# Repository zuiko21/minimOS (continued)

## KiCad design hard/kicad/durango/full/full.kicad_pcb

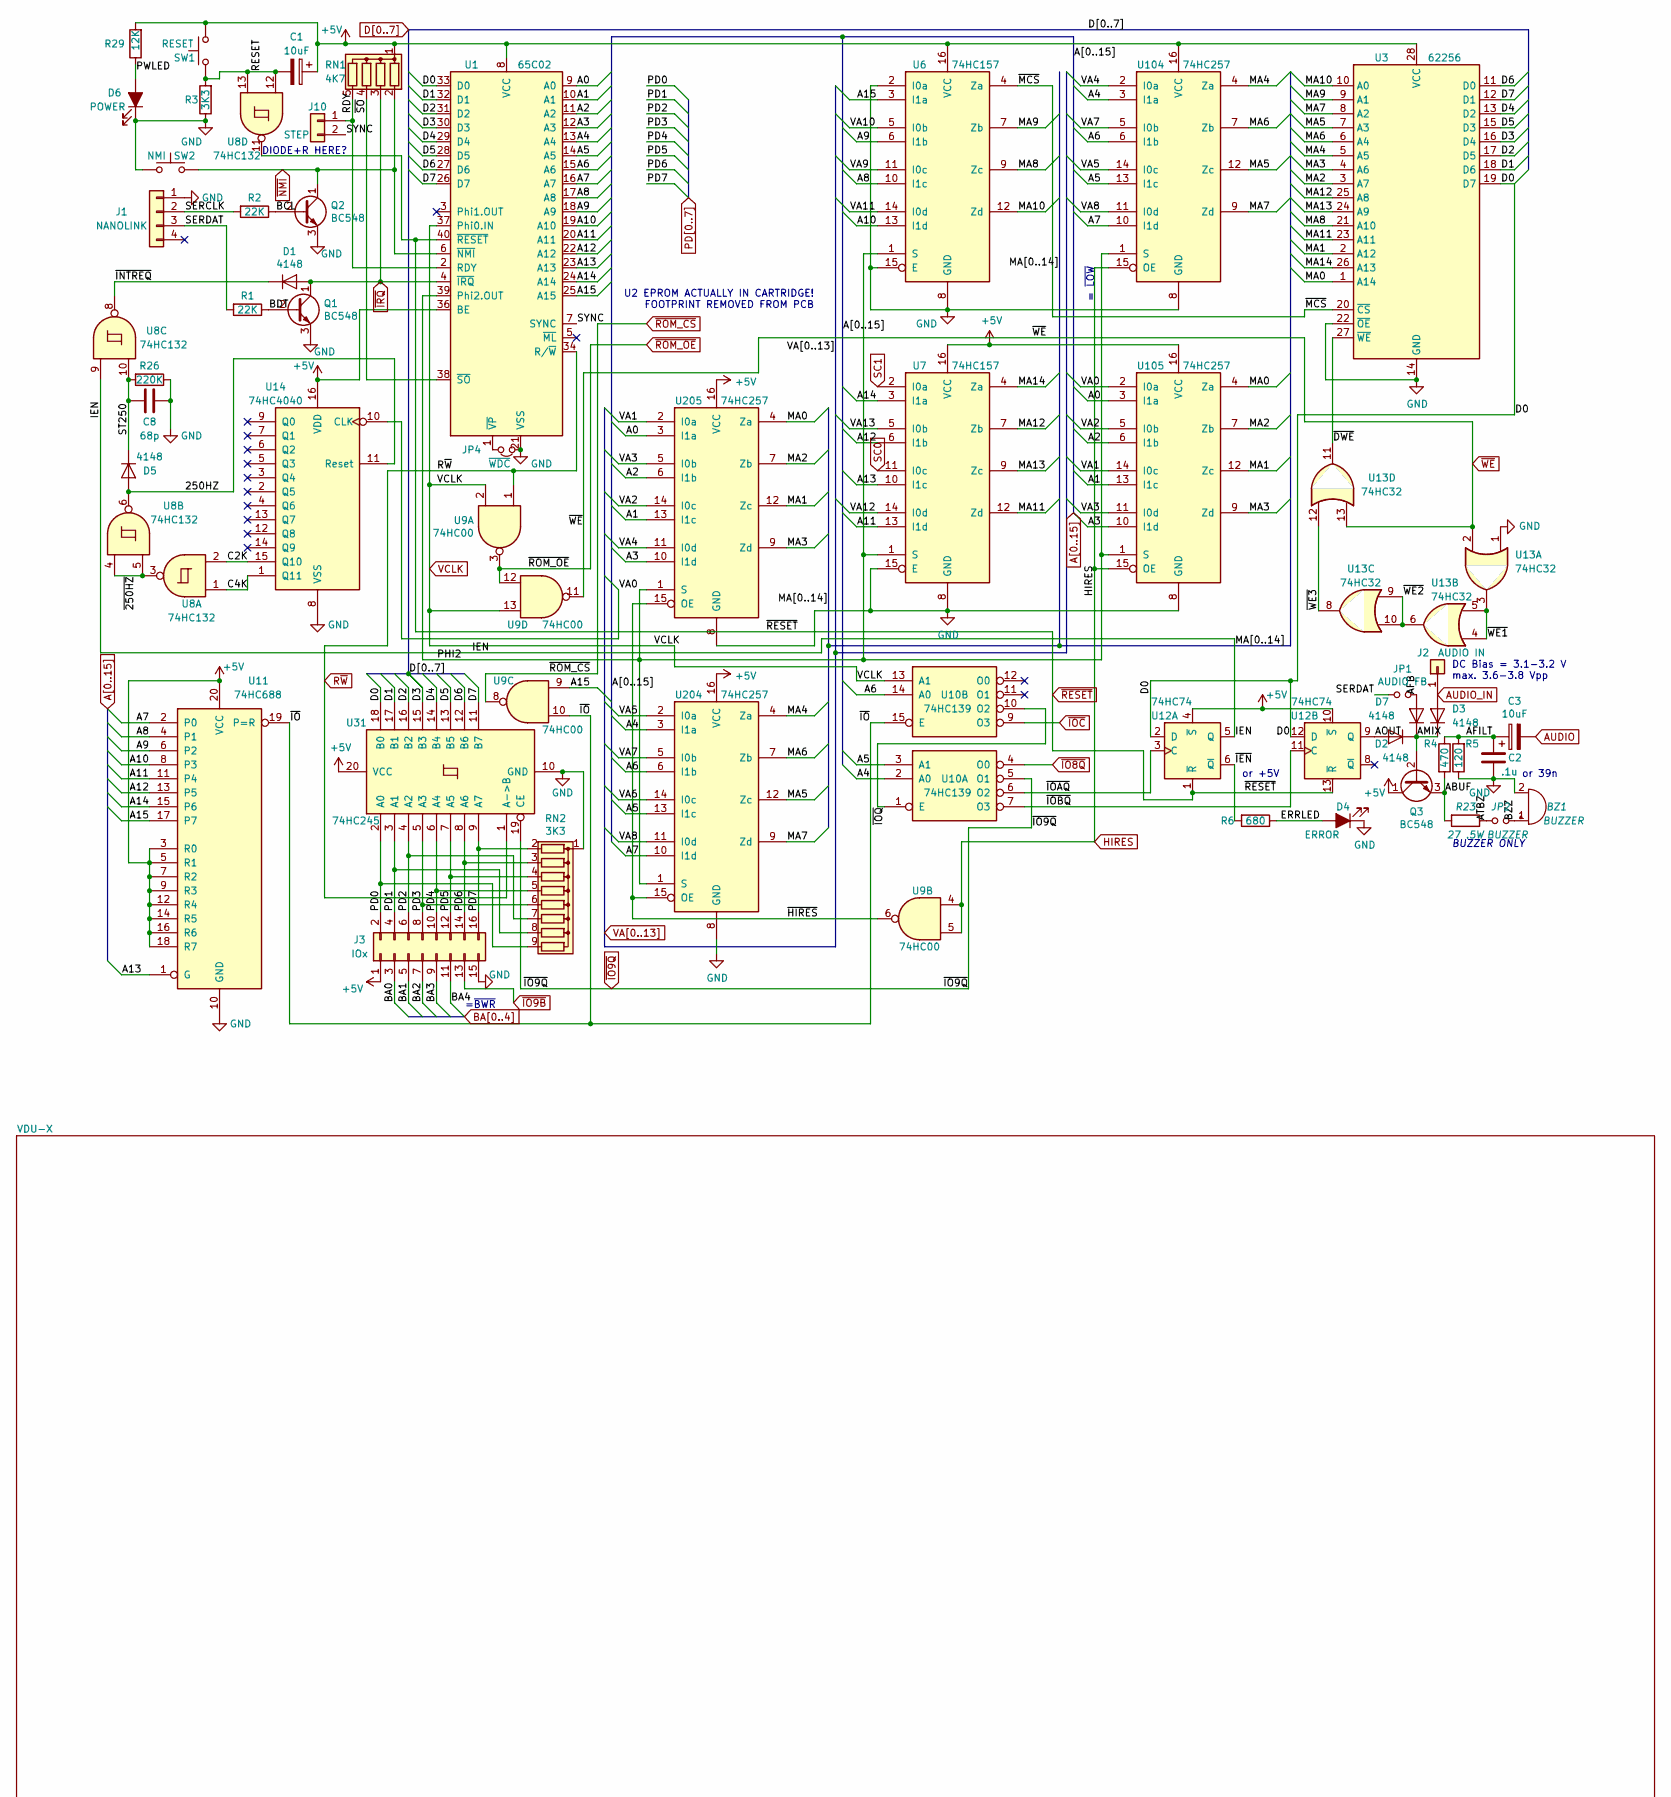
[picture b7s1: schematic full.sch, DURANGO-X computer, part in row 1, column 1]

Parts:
BZ1: BUZZER; Buzzer_12x9.5RM7.6
C1, C3: 10uF; CP_Radial_D4.0mm_P1.50mm
C2: .1u; C_Rect_L7.2mm_W2.5mm_P5.00mm_FKS2_FKP2_MKS2_MKP2
C8: 68p; C_Disc_D3.8mm_W2.6mm_P2.50mm
D1, D2, D3, D5, D7: 4148; D_DO-35_SOD27_P2.54mm_Vertical_KathodeUp
D4: ERROR; LED_D3.0mm_Clear
D6: POWER; LED_D3.0mm_Clear
J1: NANOLINK; PinHeader_1x04_P2.54mm_Vertical
J2: AUDIO IN; PinHeader_1x01_P2.54mm_Vertical
J3: IOx; IDC-Header_2x08_P2.54mm_Vertical
J10: STEP; PinHeader_1x02_P2.54mm_Vertical
JP1: AUDIO FB; PinHeader_1x02_P2.54mm_Vertical
JP2: BUZZER; PinHeader_1x02_P2.54mm_Vertical
JP4: ~WDC; SolderJumper-2_P1.3mm_Open_RoundedPad1.0x1.5mm
Q1, Q2, Q3: BC548; TO-92_Inline
R1, R2: 22K; R_Axial_DIN0207_L6.3mm_D2.5mm_P2.54mm_Vertical
R3: 3K3; R_Axial_DIN0207_L6.3mm_D2.5mm_P2.54mm_Vertical
R4: 470; R_Axial_DIN0207_L6.3mm_D2.5mm_P2.54mm_Vertical
R5: 120; R_Axial_DIN0207_L6.3mm_D2.5mm_P2.54mm_Vertical
R6: 680; R_Axial_DIN0207_L6.3mm_D2.5mm_P2.54mm_Vertical
R23: 27 .5W; R_Axial_DIN0309_L9.0mm_D3.2mm_P2.54mm_Vertical
R26: 220K; R_Axial_DIN0207_L6.3mm_D2.5mm_P2.54mm_Vertical
R29: 12K; R_Axial_DIN0207_L6.3mm_D2.5mm_P2.54mm_Vertical
RN1: 4K7; R_Array_SIP5
RN2: 3K3; R_Array_SIP9
SW1: RESET; SW_PUSH_6mm
SW2: NMI; SW_PUSH_6mm
U1: 65C02; DIP-40_W15.24mm_Socket
U3: 62256; DIP-28_W15.24mm_Socket
U6, U7: 74HC157; DIP-16_W7.62mm_Socket
U8: 74HC132; DIP-14_W7.62mm_Socket
U9: 74HC00; DIP-14_W7.62mm_Socket
U10: 74HC139; DIP-16_W7.62mm_Socket
U11: 74HC688; DIP-20_W7.62mm_Socket
U12: 74HC74; DIP-14_W7.62mm_Socket
U13: 74HC32; DIP-14_W7.62mm_Socket
U14: 74HC4040; DIP-16_W7.62mm_Socket
U31: 74HC245; DIP-20_W7.62mm_Socket
U104, U105, U204, U205: 74HC257; DIP-16_W7.62mm_Socket

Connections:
+5V: C1.1, J3.1, Q3.1 (C), R29.2, RN1.1 (common), SW1.2, U1.8 (VCC), U1.36 (BE), U3.28 (VCC), U6.16 (VCC), U7.16 (VCC), U11.3 (R0), U11.5 (R1), U11.7 (R2), U11.9 (R3), U11.12 (R4), U11.14 (R5), U11.16 (R6), U11.18 (R7), U11.20 (VCC), U12.4 (~S), U12.10 (~S), U14.16 (VDD), U31.20 (VCC), U104.16 (VCC), U105.16 (VCC), U204.16 (VCC), U205.16 (VCC); also elsewhere on the board
/250HZ: D5.2 (A), U8.6, U14.11 (Reset)
/ABUF: Q3.3 (E), R4.2, R23.2
/AFB: D7.2 (A), JP1.2
/AFILT: C2.1, C3.1, R4.1, R5.2
/AMIX: D2.1 (K), D3.1 (K), D7.1 (K), Q3.2 (B)
/AOUT: D2.2 (A), U12.9 (Q)
/ATBZ: JP2.1, R23.1
/BCL: Q2.2 (B), R2.1
/BDT: Q1.2 (B), R1.1
/BZZ: BZ1.1 (-), JP2.2
/C2K: U8.2, U14.15 (Q10)
/C4K: U8.1, U14.1 (Q11)
/ERRLED: D4.2 (A), R6.1
/IEN: U8.9, U12.5 (Q)
/MA0: U3.1 (A14), U105.4 (Za), U205.4 (Za)
/MA1: U3.2 (A12), U105.12 (Zc), U205.12 (Zc)
/MA2: U3.3 (A7), U105.7 (Zb), U205.7 (Zb)
/MA3: U3.4 (A6), U105.9 (Zd), U205.9 (Zd)
/MA4: U3.5 (A5), U104.4 (Za), U204.4 (Za)
/MA5: U3.7 (A3), U104.12 (Zc), U204.12 (Zc)
/MA6: U3.6 (A4), U104.7 (Zb), U204.7 (Zb)
/MA7: U3.8 (A2), U104.9 (Zd), U204.9 (Zd)
/MA8: U3.21 (A10), U6.9 (Zc)
/MA9: U3.9 (A1), U6.7 (Zb)
/MA10: U3.10 (A0), U6.12 (Zd)
/MA11: U3.23 (A11), U7.12 (Zd)
/MA12: U3.25 (A8), U7.7 (Zb)
/MA13: U3.24 (A9), U7.9 (Zc)
/MA14: U3.26 (A13), U7.4 (Za)
/PHI2: U1.39 (Phi2.OUT), U6.1 (S), U7.1 (S), U104.1 (S), U105.1 (S), U204.1 (S), U205.1 (S)
/PWLED: D6.2 (A), R29.1
/RDY: J10.1, RN1.5 (R4), U1.2 (RDY)
/RESET: C1.2, R3.2, SW1.1, U8.12, U8.13
/SERCLK: J1.2, R2.2
/SERDAT: J1.3, JP1.1, R1.2
/ST250: C8.2, D5.1 (K), R26.2, U8.10
/SYNC: J10.2, U1.7 (SYNC)
/~250HZ: U8.3, U8.4, U8.5
/~DWE: U3.27 (~WE~), U13.11
/~HIRES: U9.6, U204.15 (OE), U205.15 (OE)
/~IEN: R6.2, U12.6 (~Q)
/~INTREQ: D1.1 (K), U8.8
/~IO: U9.10, U10.15 (E), U11.19 (P=R)
/~IOAQ: U10.6 (O2), U12.3 (C)
/~IOBQ: U10.7 (O3), U12.11 (C)
/~IOQ: U10.1 (E), U10.10 (O2)
/~MCS: U3.20 (~CS), U6.4 (Za)
/~SO: RN1.4 (R3), U1.38 (~SO)
/~WE1: U13.3, U13.4, U13.5
/~WE2: U13.6, U13.9, U13.10
/~WE3: U13.8, U13.12
A0: U1.9 (A0), U105.3 (I1a), U205.3 (I1a); also elsewhere on the board
A1: U1.10 (A1), U105.13 (I1c), U205.13 (I1c); also elsewhere on the board
A2: U1.11 (A2), U105.6 (I1b), U205.6 (I1b); also elsewhere on the board
A3: U1.12 (A3), U105.10 (I1d), U205.10 (I1d); also elsewhere on the board
A4: U1.13 (A4), U10.2 (A0), U104.3 (I1a), U204.3 (I1a); also elsewhere on the board
A5: U1.14 (A5), U10.3 (A1), U104.13 (I1c), U204.13 (I1c); also elsewhere on the board
A6: U1.15 (A6), U10.14 (A0), U104.6 (I1b), U204.6 (I1b); also elsewhere on the board
A7: U1.16 (A7), U11.2 (P0), U104.10 (I1d), U204.10 (I1d); also elsewhere on the board
A8: U1.17 (A8), U6.10 (I1c), U11.4 (P1); also elsewhere on the board
A9: U1.18 (A9), U6.6 (I1b), U11.6 (P2); also elsewhere on the board
A10: U1.19 (A10), U6.13 (I1d), U11.8 (P3); also elsewhere on the board
A11: U1.20 (A11), U7.13 (I1d), U11.11 (P4); also elsewhere on the board
A12: U1.22 (A12), U7.6 (I1b), U11.13 (P5); also elsewhere on the board
A13: U1.23 (A13), U7.10 (I1c), U11.1 (G); also elsewhere on the board
A14: U1.24 (A14), U7.3 (I1a), U11.15 (P6); also elsewhere on the board
A15: U1.25 (A15), U6.3 (I1a), U9.9, U11.17 (P7); also elsewhere on the board
AUDIO: C3.2; also elsewhere on the board
AUDIO_IN: D3.2 (A), J2.1; also elsewhere on the board
BA0: J3.3; also elsewhere on the board
BA1: J3.5; also elsewhere on the board
BA2: J3.7; also elsewhere on the board
BA3: J3.9; also elsewhere on the board
BA4: J3.11; also elsewhere on the board
D0: U1.33 (D0), U3.19 (D7), U12.2 (D), U12.12 (D), U31.18 (B0); also elsewhere on the board
D1: U1.32 (D1), U3.18 (D6), U31.17 (B1); also elsewhere on the board
D2: U1.31 (D2), U3.17 (D5), U31.16 (B2); also elsewhere on the board
D3: U1.30 (D3), U3.16 (D4), U31.15 (B3); also elsewhere on the board
D4: U1.29 (D4), U3.13 (D2), U31.14 (B4); also elsewhere on the board
D5: U1.28 (D5), U3.15 (D3), U31.13 (B5); also elsewhere on the board
D6: U1.27 (D6), U3.11 (D0), U31.12 (B6); also elsewhere on the board
D7: U1.26 (D7), U3.12 (D1), U31.11 (B7); also elsewhere on the board
HIRES: U9.4, U9.5, U104.15 (OE), U105.15 (OE); also elsewhere on the board
unnamed: JP4.1, U1.1 (~VP)
PD0: J3.2, RN2.9 (R8), U31.2 (A0); also elsewhere on the board
PD1: J3.4, RN2.8 (R7), U31.3 (A1); also elsewhere on the board
PD2: J3.6, RN2.7 (R6), U31.4 (A2); also elsewhere on the board
PD3: J3.8, RN2.6 (R5), U31.5 (A3); also elsewhere on the board
PD4: J3.10, RN2.5 (R4), U31.6 (A4); also elsewhere on the board
PD5: J3.12, RN2.4 (R3), U31.7 (A5); also elsewhere on the board
PD6: J3.14, RN2.3 (R2), U31.8 (A6); also elsewhere on the board
PD7: J3.16, RN2.2 (R1), U31.9 (A7); also elsewhere on the board
R~W: U1.34 (R/~W), U9.1, U31.1 (A->B); also elsewhere on the board
SC0: U7.11 (I0c); also elsewhere on the board
SC1: U7.2 (I0a); also elsewhere on the board
VA0: U14.10 (CLK), U105.2 (I0a); also elsewhere on the board
VA1: U105.14 (I0c), U205.2 (I0a); also elsewhere on the board
VA2: U105.5 (I0b), U205.14 (I0c); also elsewhere on the board
VA3: U105.11 (I0d), U205.5 (I0b); also elsewhere on the board
VA4: U104.2 (I0a), U205.11 (I0d); also elsewhere on the board
VA5: U104.14 (I0c), U204.2 (I0a); also elsewhere on the board
VA6: U204.14 (I0c); also elsewhere on the board
VA7: U104.5 (I0b), U204.5 (I0b); also elsewhere on the board
VA8: U104.11 (I0d), U204.11 (I0d); also elsewhere on the board
VA9: U6.11 (I0c); also elsewhere on the board
VA10: U6.5 (I0b); also elsewhere on the board
VA11: U6.14 (I0d); also elsewhere on the board
VA12: U7.14 (I0d); also elsewhere on the board
VA13: U7.5 (I0b); also elsewhere on the board
VCLK: U1.37 (Phi0.IN), U9.2, U9.13, U10.13 (A1); also elsewhere on the board
~IO8Q: U10.4 (O0); also elsewhere on the board
~IO9B: J3.13; also elsewhere on the board
~IOC: U10.9 (O3); also elsewhere on the board
~IRQ: D1.2 (A), Q1.1 (C), RN1.3 (R2), U1.4 (~IRQ); also elsewhere on the board
~NMI: Q2.1 (C), RN1.2 (R1), SW2.1, U1.6 (~NMI); also elsewhere on the board
~RESET: U1.40 (~RESET), U8.11, U12.1 (~R), U12.13 (~R); also elsewhere on the board
~ROM_CS: U9.8; also elsewhere on the board
~ROM_OE: U9.3, U9.12; also elsewhere on the board
~WE: U9.11, U13.2, U13.13; also elsewhere on the board

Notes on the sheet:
BUZZER ONLY
DC Bias = 3.1-3.2 V max. 3.6-3.8 Vpp
or 39n
DIODE+R HERE?
or +5V
U2 EPROM ACTUALLY IN CARTRIDGE! FOOTPRINT REMOVED FROM PCB
=~BWR
= ~LOW

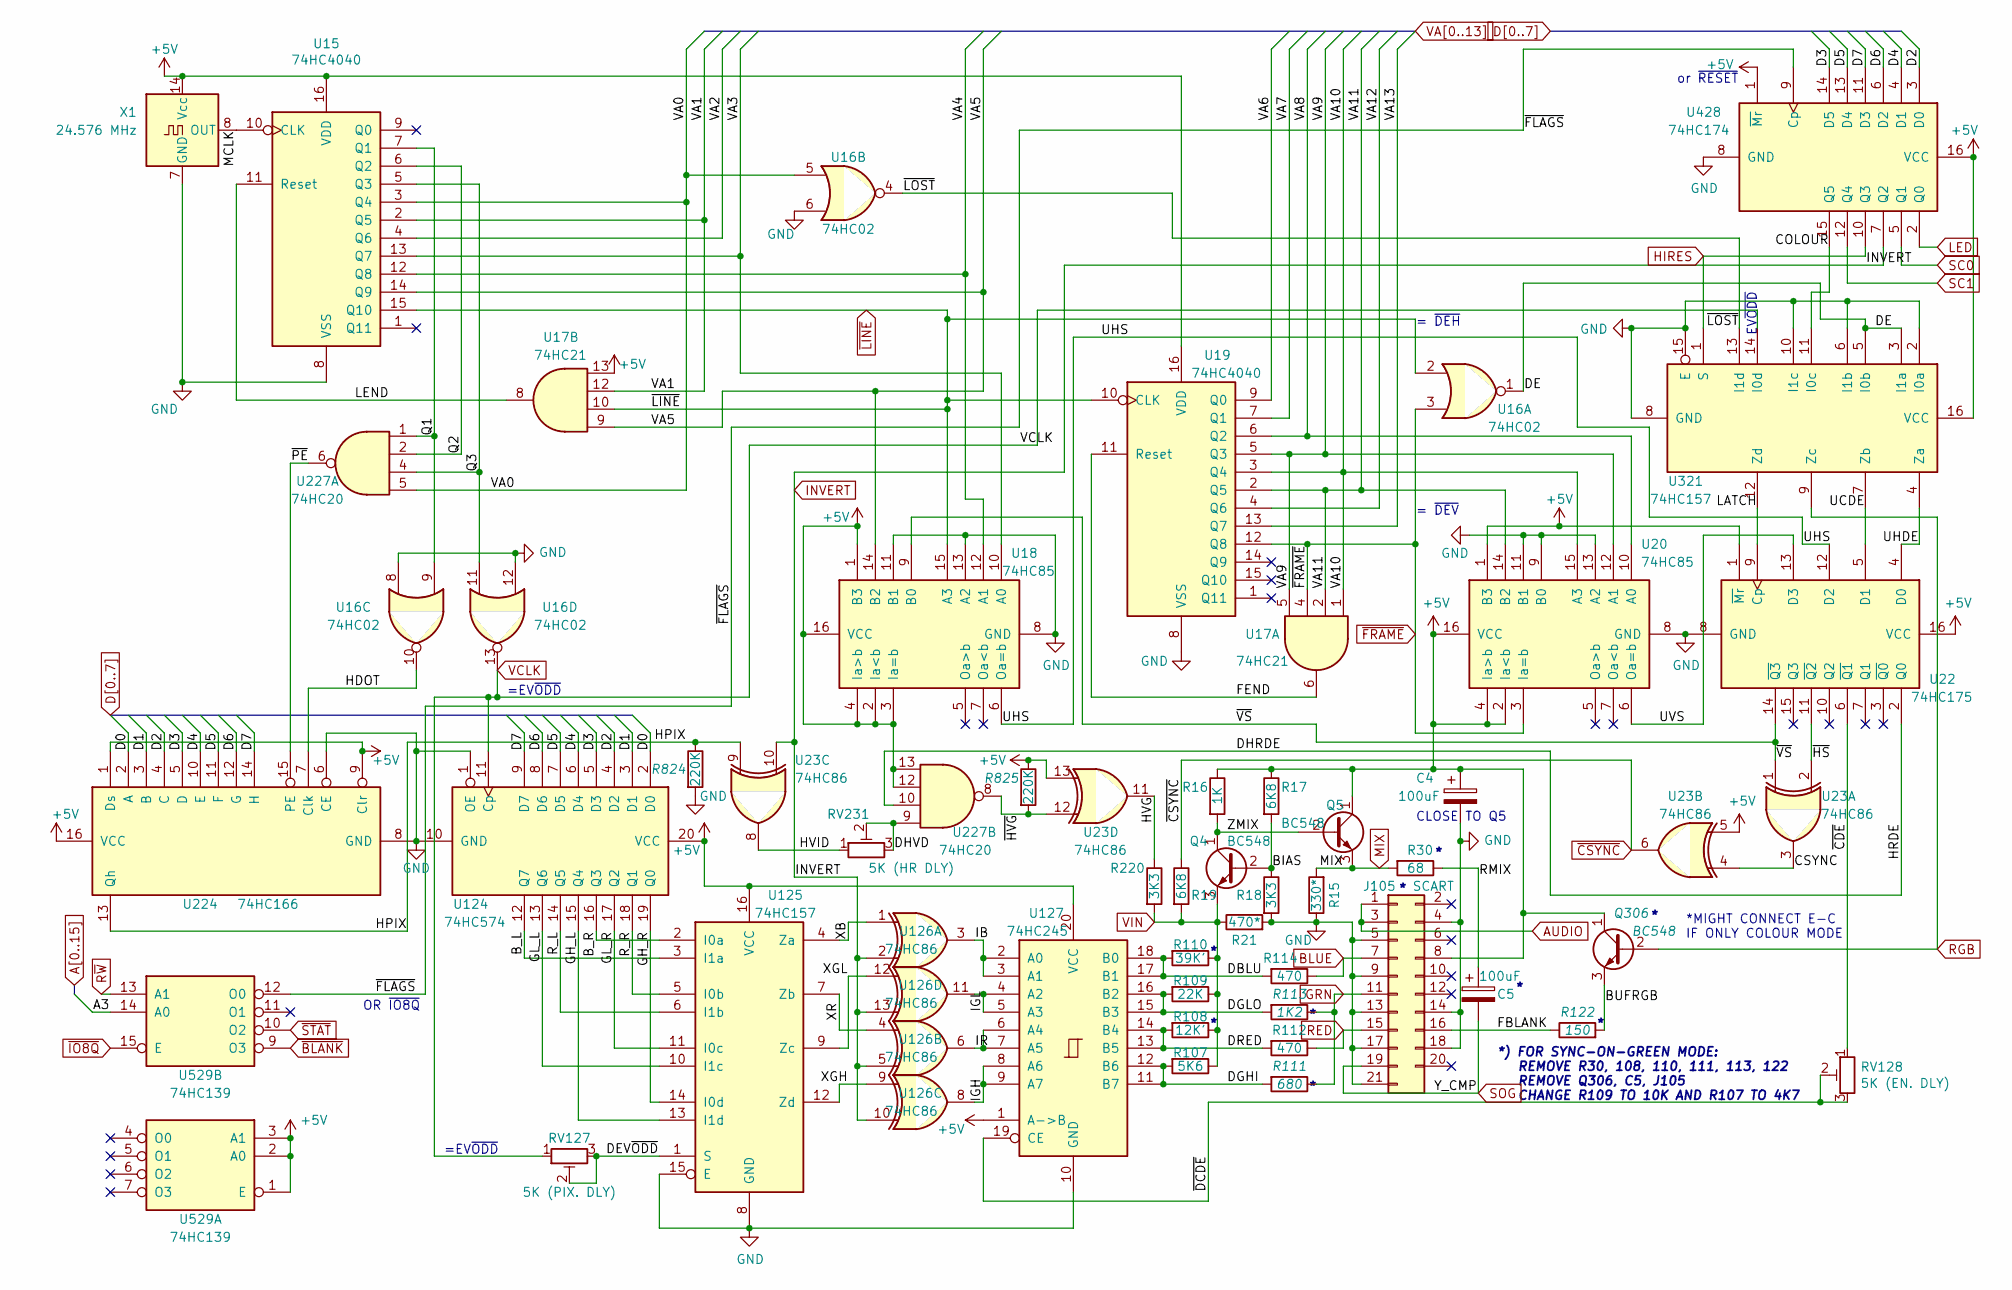
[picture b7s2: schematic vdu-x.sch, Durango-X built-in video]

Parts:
C4, C5: 100uF; CP_Radial_D4.0mm_P1.50mm
J105: SCART
Q4, Q5, Q306: BC548; TO-92_Inline
R15: 330*; R_Axial_DIN0207_L6.3mm_D2.5mm_P2.54mm_Vertical
R16: 1K; R_Axial_DIN0207_L6.3mm_D2.5mm_P2.54mm_Vertical
R17, R19: 6K8; R_Axial_DIN0207_L6.3mm_D2.5mm_P2.54mm_Vertical
R18, R220: 3K3; R_Axial_DIN0207_L6.3mm_D2.5mm_P2.54mm_Vertical
R21: 470*; R_Axial_DIN0207_L6.3mm_D2.5mm_P2.54mm_Vertical
R30: 68; R_Axial_DIN0207_L6.3mm_D2.5mm_P2.54mm_Vertical
R107: 5K6; R_Axial_DIN0207_L6.3mm_D2.5mm_P2.54mm_Vertical
R108: 12K'; R_Axial_DIN0207_L6.3mm_D2.5mm_P2.54mm_Vertical
R109: 22K; R_Axial_DIN0207_L6.3mm_D2.5mm_P2.54mm_Vertical
R110: 39K'; R_Axial_DIN0207_L6.3mm_D2.5mm_P2.54mm_Vertical
R111: 680; R_Axial_DIN0207_L6.3mm_D2.5mm_P2.54mm_Vertical
R112, R114: 470; R_Axial_DIN0207_L6.3mm_D2.5mm_P2.54mm_Vertical
R113: 1K2; R_Axial_DIN0207_L6.3mm_D2.5mm_P2.54mm_Vertical
R122: 150; R_Axial_DIN0207_L6.3mm_D2.5mm_P2.54mm_Vertical
R824, R825: 220K; R_Axial_DIN0207_L6.3mm_D2.5mm_P2.54mm_Vertical
RV127: 5K (PIX. DLY); Potentiometer_Piher_PT-6-V_Vertical
RV128: 5K (EN. DLY); Potentiometer_Piher_PT-6-V_Vertical
RV231: 5K (HR DLY); Potentiometer_Piher_PT-6-V_Vertical
U15, U19: 74HC4040; DIP-16_W7.62mm_Socket
U16: 74HC02; DIP-14_W7.62mm_Socket
U17: 74HC21; DIP-14_W7.62mm_Socket
U18, U20: 74HC85; DIP-16_W7.62mm_Socket
U22: 74HC175; DIP-16_W7.62mm_Socket
U23, U126: 74HC86; DIP-14_W7.62mm_Socket
U124: 74HC574; DIP-20_W7.62mm_Socket
U125, U321: 74HC157; DIP-16_W7.62mm_Socket
U127: 74HC245; DIP-20_W7.62mm_Socket
U224: 74HC166; DIP-16_W7.62mm_Socket
U227: 74HC20; DIP-14_W7.62mm_Socket
U428: 74HC174; DIP-16_W7.62mm_Socket
U529: 74HC139; DIP-16_W7.62mm_Socket
X1: 24.576 MHz; Oscillator_DIP-14

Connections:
+5V: C4.1, J105.8, Q5.1 (C), Q306.1 (C), R16.1, R17.1, R825.1, U15.16 (VDD), U17.13, U18.1 (B3), U18.2 (Ia<b), U18.3 (Ia=b), U18.4 (Ia>b), U18.16 (VCC), U19.16 (VDD), U20.1 (B3), U20.2 (Ia<b), U20.4 (Ia>b), U20.16 (VCC), U22.1 (~Mr), U22.16 (VCC), U23.5, U23.13, U124.20 (VCC), U125.16 (VCC), U127.1 (A->B), U127.20 (VCC), U224.1 (Ds), U224.9 (Clr), U224.16 (VCC), U227.12, U227.13, U321.16 (VCC), U428.1 (~Mr), U428.16 (VCC), U529.1 (E), U529.2 (A0), U529.3 (A1), X1.14 (Vcc); also elsewhere on the board
/VDU-X/BIAS: Q4.2 (B), R17.2, R18.1
/VDU-X/BUFRGB: Q306.3 (E), R122.2
/VDU-X/B_L: U124.12 (Q7), U125.3 (I1a)
/VDU-X/B_R: U124.16 (Q3), U125.2 (I0a)
/VDU-X/COLOUR: U321.11 (I0c), U428.15 (Q5)
/VDU-X/CSYNC: U23.3, U23.4
/VDU-X/DBLU: R110.2, R114.2, U127.17 (B1), U127.18 (B0)
/VDU-X/DE: U16.1, U321.3 (I1a), U321.5 (I0b)
/VDU-X/DEV~ODD: RV127.2, RV127.3, U125.1 (S)
/VDU-X/DGHI: R107.2, R111.2, U127.11 (B7), U127.12 (B6)
/VDU-X/DGLO: R109.2, R113.2, U127.15 (B3), U127.16 (B2)
/VDU-X/DHRDE: U22.2 (Q0), U227.10
/VDU-X/DHVD: RV231.2, RV231.3, U227.9
/VDU-X/DRED: R108.2, R112.2, U127.13 (B5), U127.14 (B4)
/VDU-X/FBLANK: J105.16, R122.1
/VDU-X/FEND: U17.6, U19.11 (Reset)
/VDU-X/GH_L: U124.15 (Q4), U125.13 (I1d)
/VDU-X/GH_R: U124.19 (Q0), U125.14 (I0d)
/VDU-X/GL_L: U124.13 (Q6), U125.10 (I1c)
/VDU-X/GL_R: U124.17 (Q2), U125.11 (I0c)
/VDU-X/HDOT: U16.10, U224.7 (Clk)
/VDU-X/HPIX: R824.1, U23.9, U224.13 (Qh)
/VDU-X/HVG: R220.1, U23.11
/VDU-X/HVID: RV231.1, U23.8
/VDU-X/IB: U126.3, U127.2 (A0), U127.3 (A1)
/VDU-X/IGH: U126.8, U127.8 (A6), U127.9 (A7)
/VDU-X/IGL: U126.11, U127.4 (A2), U127.5 (A3)
/VDU-X/IR: U126.6, U127.6 (A4), U127.7 (A5)
/VDU-X/LATCH: U22.9 (Cp), U321.12 (Zd)
/VDU-X/LEND: U15.11 (Reset), U17.8
/VDU-X/MCLK: U15.10 (CLK), X1.8 (OUT)
/VDU-X/Q1: U15.7 (Q1), U16.9, U227.1
/VDU-X/Q2: U15.6 (Q2), U227.2
/VDU-X/Q3: U15.5 (Q3), U16.11, U227.4
/VDU-X/RMIX: C5.1, R30.1
/VDU-X/R_L: U124.14 (Q5), U125.6 (I1b)
/VDU-X/R_R: U124.18 (Q1), U125.5 (I0b)
/VDU-X/UCDE: U22.5 (D1), U321.7 (Zb)
/VDU-X/UHDE: U22.4 (D0), U321.4 (Za)
/VDU-X/UHS: U18.6 (Oa=b), U22.12 (D2)
/VDU-X/UVS: U20.6 (Oa=b), U22.13 (D3)
/VDU-X/XB: U125.4 (Za), U126.1
/VDU-X/XGH: U125.12 (Zd), U126.9
/VDU-X/XGL: U125.9 (Zc), U126.12
/VDU-X/XR: U125.7 (Zb), U126.4
/VDU-X/ZMIX: Q4.1 (C), Q5.2 (B), R16.2
/VDU-X/~CDE: RV128.1, U22.6 (~Q1)
/VDU-X/~DCDE: RV128.2, RV128.3, U127.19 (CE)
/VDU-X/~FLAGS: U428.9 (Cp), U529.12 (O0)
/VDU-X/~HS: U22.11 (~Q2), U23.2
/VDU-X/~HVG: R825.2, U23.12, U227.8
/VDU-X/~LOST: U16.4, U321.13 (I1d)
/VDU-X/~PE: U224.15 (PE), U227.6
/VDU-X/~VS: U18.9 (B0), U22.14 (~Q3), U23.1
A3: U529.14 (A0); also elsewhere on the board
AUDIO: J105.1, J105.3; also elsewhere on the board
BLUE: J105.7, R114.1; also elsewhere on the board
D0: U124.2 (D0), U224.2 (A); also elsewhere on the board
D1: U124.3 (D1), U224.3 (B); also elsewhere on the board
D2: U124.4 (D2), U224.4 (C), U428.3 (D0); also elsewhere on the board
D3: U124.5 (D3), U224.5 (D), U428.14 (D5); also elsewhere on the board
D4: U124.6 (D4), U224.10 (E), U428.4 (D1); also elsewhere on the board
D5: U124.7 (D5), U224.11 (F), U428.13 (D4); also elsewhere on the board
D6: U124.8 (D6), U224.12 (G), U428.6 (D2); also elsewhere on the board
D7: U124.9 (D7), U224.14 (H), U428.11 (D3); also elsewhere on the board
GRN: J105.11, R111.1, R113.1; also elsewhere on the board
HIRES: U321.1 (S), U428.10 (Q3); also elsewhere on the board
INVERT: U23.10, U126.2, U126.5, U126.10, U126.13, U428.7 (Q2); also elsewhere on the board
LED: U428.2 (Q0); also elsewhere on the board
MIX: Q5.3 (E), R15.2, R30.2; also elsewhere on the board
RED: J105.15, R112.1; also elsewhere on the board
RGB: Q306.2 (B), U321.9 (Zc); also elsewhere on the board
R~W: U529.13 (A1); also elsewhere on the board
SC0: U428.5 (Q1); also elsewhere on the board
SC1: U428.12 (Q4); also elsewhere on the board
SOG: C5.2, J105.19; also elsewhere on the board
VA0: U15.3 (Q4), U16.5, U227.5; also elsewhere on the board
VA1: U15.2 (Q5), U17.12; also elsewhere on the board
VA2: U15.4 (Q6); also elsewhere on the board
VA3: U15.13 (Q7), U18.10 (A0); also elsewhere on the board
VA4: U15.12 (Q8), U18.12 (A1); also elsewhere on the board
VA5: U15.14 (Q9), U17.9, U18.14 (B2); also elsewhere on the board
VA6: U19.9 (Q0); also elsewhere on the board
VA7: U19.7 (Q1); also elsewhere on the board
VA8: U19.6 (Q2), U20.10 (A0); also elsewhere on the board
VA9: U17.5, U19.5 (Q3), U20.12 (A1); also elsewhere on the board
VA10: U17.1, U19.3 (Q4), U20.15 (A3); also elsewhere on the board
VA11: U17.2, U19.2 (Q5), U20.14 (B2); also elsewhere on the board
VA12: U19.4 (Q6); also elsewhere on the board
VA13: U19.13 (Q7); also elsewhere on the board
VCLK: RV127.1, U16.13, U124.11 (Cp), U321.14 (I0d); also elsewhere on the board
VIN: Q4.3 (E), R19.2, R21.1, R107.1, R108.1, R109.1, R110.1, R220.2; also elsewhere on the board
~BLANK: U529.9 (O3); also elsewhere on the board
~CSYNC: R19.1, U23.6; also elsewhere on the board
~FRAME: U16.3, U17.4, U19.12 (Q8), U20.3 (Ia=b); also elsewhere on the board
~IO8Q: U529.15 (E); also elsewhere on the board
~LINE: U15.15 (Q10), U16.2, U17.10, U18.15 (A3), U19.10 (CLK); also elsewhere on the board
~STAT: U529.10 (O2); also elsewhere on the board

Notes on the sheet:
*) FOR SYNC-ON-GREEN MODE: REMOVE R30, 108, 110, 111, 113, 122 REMOVE Q306, C5, J105 CHANGE R109 TO 10K AND R107 TO 4K7
*MIGHT CONNECT E-C IF ONLY COLOUR MODE
OR ~IO8Q
or ~RESET
CLOSE TO Q5
=EV~ODD
= ~DEH
= ~DEV
EV~ODD

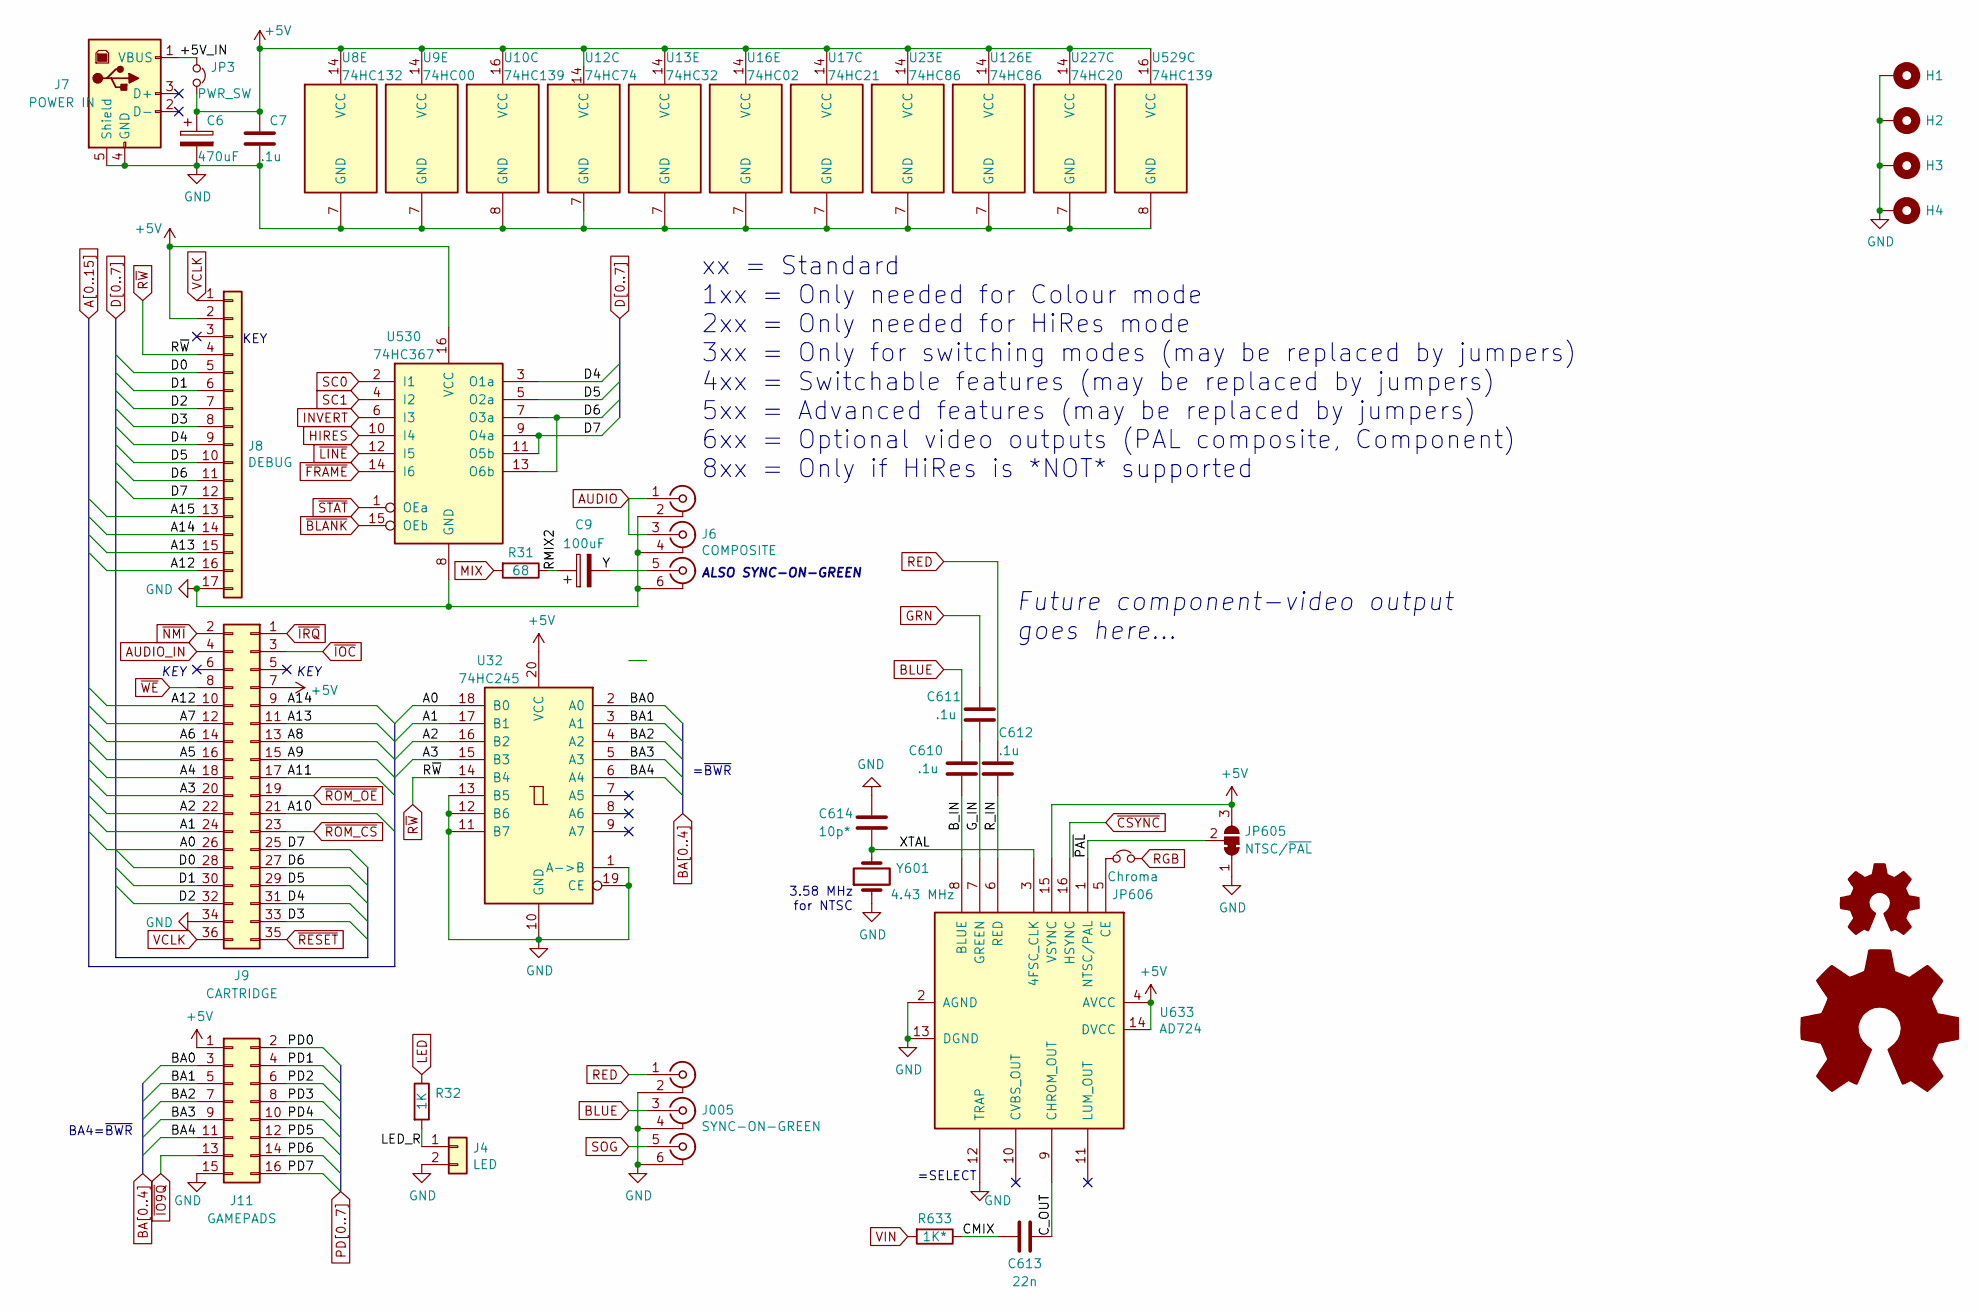
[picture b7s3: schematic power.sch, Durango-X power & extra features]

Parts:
C6: 470uF; CP_Radial_D6.3mm_P2.50mm
C7, C610, C611, C612: .1u; C_Rect_L7.2mm_W2.5mm_P5.00mm_FKS2_FKP2_MKS2_MKP2
C9: 100uF; CP_Radial_D4.0mm_P1.50mm
C613: 22n; C_Disc_D6.0mm_W2.5mm_P5.00mm
C614: 10p*; C_Disc_D3.8mm_W2.6mm_P2.50mm
H1, H2, H3, H4: MountingHole_3.2mm_M3_DIN965_Pad
J4: LED; PinHeader_1x02_P2.54mm_Vertical
J005: SYNC-ON-GREEN; 3xRCA
J6: COMPOSITE; 3xRCA
J7: POWER IN; USB_B_OST_USB-B1HSxx_Horizontal
J8: DEBUG; PinSocket_1x17_P2.54mm_Vertical
J9: CARTRIDGE; PinSocket_2x18_EDGE
J11: GAMEPADS; PinSocket_2x08_P2.54mm_Horizontal
JP3: PWR_SW; PinHeader_1x02_P2.54mm_Vertical
JP605: NTSC/~PAL; SolderJumper-3_P1.3mm_Bridged12_RoundedPad1.0x1.5mm
JP606: Chroma; PinHeader_1x02_P2.54mm_Vertical
LOGO1: OSHW-Logo2_14.6x12mm_SilkScreen
LOGO2: durango-x
R31: 68; R_Axial_DIN0207_L6.3mm_D2.5mm_P2.54mm_Vertical
R32: 1K; R_Axial_DIN0207_L6.3mm_D2.5mm_P2.54mm_Vertical
R633: 1K*; R_Axial_DIN0207_L6.3mm_D2.5mm_P2.54mm_Vertical
U8: 74HC132; DIP-14_W7.62mm_Socket
U9: 74HC00; DIP-14_W7.62mm_Socket
U10, U529: 74HC139; DIP-16_W7.62mm_Socket
U12: 74HC74; DIP-14_W7.62mm_Socket
U13: 74HC32; DIP-14_W7.62mm_Socket
U16: 74HC02; DIP-14_W7.62mm_Socket
U17: 74HC21; DIP-14_W7.62mm_Socket
U23, U126: 74HC86; DIP-14_W7.62mm_Socket
U32: 74HC245; DIP-20_W7.62mm_Socket
U227: 74HC20; DIP-14_W7.62mm_Socket
U530: 74HC367; DIP-16_W7.62mm_Socket
U633: AD724; SOIC-16W_7.5x10.3mm_P1.27mm
Y601: 4.43 MHz; Crystal_HC49-4H_Vertical

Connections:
+5V: C6.1, C7.1, J8.2, J9.7, J11.1, JP3.2, JP605.3 (B), U8.14 (VCC), U9.14 (VCC), U10.16 (VCC), U12.14 (VCC), U13.14 (VCC), U16.14 (VCC), U17.14 (VCC), U23.14 (VCC), U32.20 (VCC), U126.14 (VCC), U227.14 (VCC), U529.16 (VCC), U530.16 (VCC), U633.4 (AVCC), U633.14 (DVCC), U633.15 (VSYNC); also elsewhere on the board
/power/+5V_IN: J7.1 (VBUS), JP3.1
/power/B_IN: C610.2, U633.8 (BLUE)
/power/CMIX: C613.2, R633.1
/power/C_EN: JP606.1, U633.5 (CE); also elsewhere on the board
/power/C_OUT: C613.1, U633.9 (CHROM_OUT)
/power/G_IN: C611.2, U633.7 (GREEN)
/power/LED_R: J4.1, R32.2
/power/RMIX2: C9.1, R31.1
/power/R_IN: C612.2, U633.6 (RED)
/power/XTAL: C614.2, U633.3 (4FSC_CLK), Y601.2
/power/Y: C9.2, J6.5 (IN3)
/power/~PAL: JP605.2 (C), U633.1 (NTSC/PAL)
A0: J9.26, U32.18 (B0); also elsewhere on the board
A1: J9.24, U32.17 (B1); also elsewhere on the board
A2: J9.22, U32.16 (B2); also elsewhere on the board
A3: J9.20, U32.15 (B3); also elsewhere on the board
A4: J9.18; also elsewhere on the board
A5: J9.16; also elsewhere on the board
A6: J9.14; also elsewhere on the board
A7: J9.12; also elsewhere on the board
A8: J9.13; also elsewhere on the board
A9: J9.15; also elsewhere on the board
A10: J9.21; also elsewhere on the board
A11: J9.17; also elsewhere on the board
A12: J8.16, J9.10; also elsewhere on the board
A13: J8.15, J9.11; also elsewhere on the board
A14: J8.14, J9.9; also elsewhere on the board
A15: J8.13; also elsewhere on the board
AUDIO: J6.1 (IN1), J6.3 (IN2); also elsewhere on the board
AUDIO_IN: J9.4; also elsewhere on the board
BA0: J11.3, U32.2 (A0); also elsewhere on the board
BA1: J11.5, U32.3 (A1); also elsewhere on the board
BA2: J11.7, U32.4 (A2); also elsewhere on the board
BA3: J11.9, U32.5 (A3); also elsewhere on the board
BA4: J11.11, U32.6 (A4); also elsewhere on the board
BLUE: C610.1, J005.3 (IN2); also elsewhere on the board
D0: J8.5, J9.28; also elsewhere on the board
D1: J8.6, J9.30; also elsewhere on the board
D2: J8.7, J9.32; also elsewhere on the board
D3: J8.8, J9.33; also elsewhere on the board
D4: J8.9, J9.31, U530.3 (O1a); also elsewhere on the board
D5: J8.10, J9.29, U530.5 (O2a); also elsewhere on the board
D6: J8.11, J9.27, U530.7 (O3a), U530.13 (O6b); also elsewhere on the board
D7: J8.12, J9.25, U530.9 (O4a), U530.11 (O5b); also elsewhere on the board
GRN: C611.1; also elsewhere on the board
HIRES: U530.10 (I4); also elsewhere on the board
INVERT: U530.6 (I3); also elsewhere on the board
LED: R32.1; also elsewhere on the board
MIX: R31.2; also elsewhere on the board
PD0: J11.2; also elsewhere on the board
PD1: J11.4; also elsewhere on the board
PD2: J11.6; also elsewhere on the board
PD3: J11.8; also elsewhere on the board
PD4: J11.10; also elsewhere on the board
PD5: J11.12; also elsewhere on the board
PD6: J11.14; also elsewhere on the board
PD7: J11.16; also elsewhere on the board
RED: C612.1, J005.1 (IN1); also elsewhere on the board
RGB: JP606.2; also elsewhere on the board
R~W: J8.4, U32.14 (B4); also elsewhere on the board
SC0: U530.2 (I1); also elsewhere on the board
SC1: U530.4 (I2); also elsewhere on the board
SOG: J005.5 (IN3); also elsewhere on the board
VCLK: J8.1, J9.36; also elsewhere on the board
VIN: R633.2; also elsewhere on the board
~BLANK: U530.15 (OEb); also elsewhere on the board
~CSYNC: U633.16 (HSYNC); also elsewhere on the board
~FRAME: U530.14 (I6); also elsewhere on the board
~IO9B: U32.7 (A5); also elsewhere on the board
~IOC: J9.3; also elsewhere on the board
~IRQ: J9.1; also elsewhere on the board
~LINE: U530.12 (I5); also elsewhere on the board
~NMI: J9.2; also elsewhere on the board
~RESET: J9.35; also elsewhere on the board
~ROM_CS: J9.23; also elsewhere on the board
~ROM_OE: J9.19; also elsewhere on the board
~STAT: U530.1 (OEa); also elsewhere on the board
~WE: J9.8; also elsewhere on the board

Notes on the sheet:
KEY
xx = Standard 1xx = Only needed for Colour mode 2xx = Only needed for HiRes mode 3xx = Only for switching modes (may be replaced by jumpers) 4xx = Switchable features (may be replaced by jumpers) 5xx = Advanced features (may be replaced by jumpers) 6xx = Optional video outputs (PAL composite, Compo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
Future component-video output goes here…
ALSO SYNC-ON-GREEN
=~BWR
BA4=~BWR
=SELECT
3.58 MHz for NTSC

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
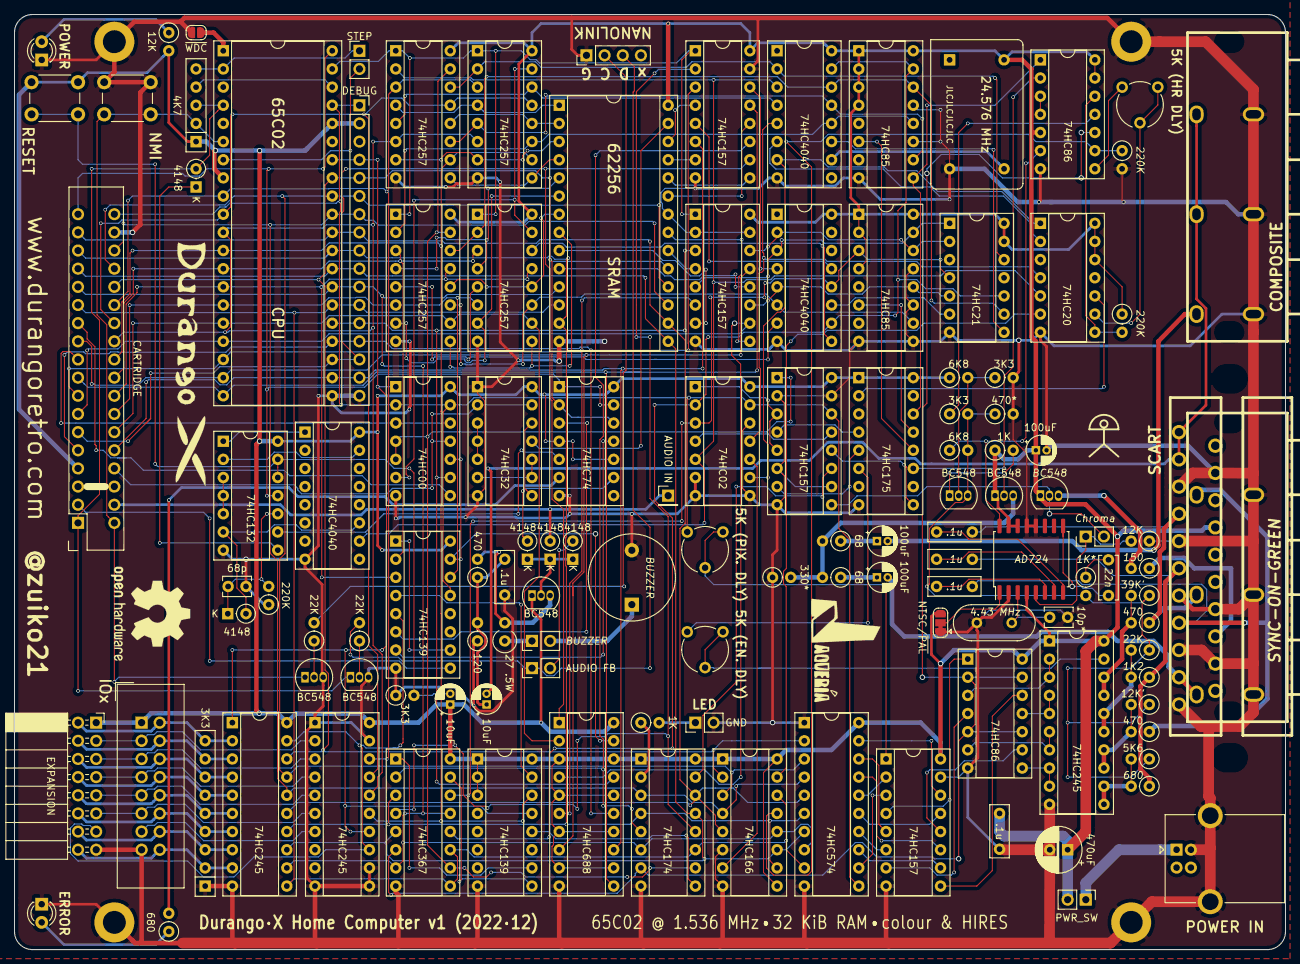
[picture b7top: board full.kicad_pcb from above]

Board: 2 copper layers, 177.8 x 130.8 mm, 130 parts (0 on the bottom side), 202 nets.

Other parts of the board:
LOGO3: jaqueria
R634: 12K; R_Axial_DIN0207_L6.3mm_D2.5mm_P2.54mm_Vertical

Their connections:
/power/C_EN: R634.2; also elsewhere on the board
